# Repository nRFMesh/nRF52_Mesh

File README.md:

# Discussions
get support, give feedback or simply chat to brainstorm about ideas right here on github with s special forum for this project

https://github.com/nRFMesh/nRF52_Mesh/discussions

# New repo nRF52 Zephyr Mesh Ultrawideband
this repo is in hybernation mode and based on the nRF-SDK, new development targetting openthread on nRF52840 sensor tag based on nRF-Connect/Zephyr is ongoing on this repo https://github.com/HomeSmartMesh/sdk-hsm-sensortag

# Features

* 2.4 GHz 2 Mbps Mesh Network
  * tested with 300 packets / second
* Flash time automated database config
* Zero install time configuration
  * No association, No pairing, No factory resets
* Router = Coordinator = Repeater = Sniffer = CLI
* text serial line protocol
* Multiple Network endpoints
  * No single point of failure
* Server, Dongles, Sensors
  * Full Stack Open Source (no softdevices required)
  * HW On the shelves
  * optional DIY HW
* Alive trace routing
  * a heartbeat message that gives info about the age and RF tx/rx hops through the route

see below the [Drivers & Custom Mesh protocol](#Drivers-&-Custom-Mesh-protocol) section for the RF Protocol details

# Description
* 2 Mbps (e.g. Zgibee is at 250 Kbps to have a higher range), lowering the bitrate does not improve the range enough to get rid of repeaters, and once you need repeaters these are continuous listeners and require permanent power anyway, so the strategy is to have a repeater for every slot of the house and those repeaters can have power amplifiers and the range problem is solved keeping the high bitrate feature.
* successfull stress tests including up to 300 packets / second.
* This [nodes.json](./nodes.json) configuration file contains the short id for device unique identifier (uid64) and other configurations such as the channel, the sleep time, the required function,... Note that a python script using jLink API automate the flashing process as the uid is read every time from the attached device and matches the parameters to be flashed from the config file.
* As the short id (8 bits) is flashed, there is no association process required and all sensor devices can act as a pure beacons (no listening required) which considerably increases battery life time. We can keep arguing about the need of an acknowledged protocol for sensors logging, I do not think it is required as the feedback of battery level and rssi are both logged as well so the user knows if the sensor is in a healthy position or not.
* Router = Coordinator = Repeater = Sniffer = CLI : actually, a configuration activates the repeat functionality in case someone wants a completely stealth sniffer and this config does not require a different FW. There is nothing to coordinate as the mesh is fully dynamic with a flood and time to live concept. And every dongle has a CLI in text mode to report heard packets and takes commands as text input.
* A consequence of the simplified design allows to have multiple dongles in different locations listening to the network and reporting it to mqtt which avoids any single point of failure. By design there is no id 0 privileged coordinator and end devices do not require to know any particular associated address, they just wake up, broadcast and sleep.
* As visible in the gif animations below, Open Source SW is provided for all steps, devices firmware and server python code.

# Static Demo

* [UART : dongle firmware - directory](https://github.com/nRFMesh/nRF52_Mesh/tree/master/applications/04_uart_dongle)
* [USB : dongle firmware - directory](https://github.com/nRFMesh/nRF52_Mesh/tree/master/applications/08_usb_dongle)

    cu -l /dev/ttyACM0 -s 460800 

subscribe to topic

    mosquitto_sub -t 'nrf/#' -v | ts

start nrf_mesh [py/nrf_mesh](https://github.com/HomeSmartMesh/raspi/tree/master/py/nrf_mesh) from [raspi](https://github.com/HomeSmartMesh/raspi/) Project

    python3 nrf_mesh.py

This custom sensors RF mesh can expand to cover a home area. Onces connected to services provided in the [raspi](https://github.com/HomeSmartMesh/raspi) project, including python scripts, influxdb and grafana, the end result dashboard looks like this

---

# nRF52 Applications
    cd ./applications/

only the main applications are listed here, for further details about all applications see below the [More nRF52 Applications](#More-nRF52-Applications) section

## 01 sensor tag
    application/01_sensortag> make flash
    application/01_sensortag> make paramw

* Status : deployed > 1 year
* nRF52832 module
* Temperature, Humidity, Pressure : BME280
* Light : MAX44009
* Smooth graphana logs with cyclic broadcast ~ 30 sec => battery life ~ 6 month on CR2032
* `make paramw` detects the device uid and writes the config parameters available in [nodes.json](./nodes.json)

## 04 uart dongle
    application/04_uart_dongle> make flash
    application/04_uart_dongle> make paramw

* Status : deployed > 1 year
* buy : "nRF52832 BLE USB UART dongle"
* custom firmware and pogo-pins jtag adapter see below
* RF Mesh repeater + RF Mesh to Host interface
* `make paramw` detects the device uid and writes the config parameters available in [nodes.json](./nodes.json)

## 08 usb dongle (nRF52840-dongle)
    application/08_usb_dongle> make flash
    application/08_usb_dongle> make paramw

* buy : "nRF52840 usb dongle"
* custom firmware for RF mesh
* RF Mesh repeater + RF Mesh to Host interface
* buffered USB CDC tx and rx
* `make paramw` detects the device uid and writes the config parameters available in [nodes.json](./nodes.json)
* pogo-pins jtag adapter 3dprint : 
  * [Version two CAD Model](https://a360.co/3jr91PD)
  * [Version one Fusion360 CAD model](https://a360.co/2CDqeTA)

---

# Drivers & Custom Mesh protocol

    cd ./drivers/

## ./drivers/

Contains the custom drivers for this project from which the [mesh.c](./drivers/mesh.c) a light weight Mesh Protocol connecting all the devices using a custom RF protocol (without softdevice)
* Sleepy nodes (low power) and router nodes (always listening)
* single layer ultra simple rpotocol. App into mac with unique ids to small ids mapping
* A simple alternative to the Bluetooth Mesh and Zigbee Thread IPV6

* Low power node : Mesh node that can be a sensor Tag that wakes up on RTC or on sensor value interrupt to log a parameter. Can also be a button that wakes up on a press PIO interrupt.
* Router node : Mesh node that cooperates with the Low power nodes, the router has to be a device that keeps listening permanently on the same RF channel, this might require ~ 13 mA. Example router devices are light controllers, server’s RF dongle or USB powered sensors and status devices.
* Server : A Raspberry pi running linux. The RF signals come through the serial port or with a USB adapter, then published on MQTT, from which Python scripts inject signals on the Database, connected to Grafana web server. Note that there can be multiple router dongles connected to servers.

## Protocol Overview

The Home Smart Mesh project introduce an RF Mesh protocol which is a complete stack implementation to allow devices to communicate in a Mesh Network Topology. This protocol implementation is using the nRF SDK 15 it is using the Radio module through a modified Enhanced Shock-burst custom protocol. Implementations range from nRF24L01+ with an STM8L and STM32 to the nRF51 and nRF52 families that add features such as RSSI and bigger packets sizes.

## Protocol Description

* 100% Open source Mesh RF Stack
* Ported on STM8L, STM32, nRF51 and nRF52
* Concept designed for Low Power Nodes and Router Nodes
* Same radio channel configured for the whole network
* Single channel allows maximum power save with unlimited sleep periods, and random wake up with button press or sensor event.
* Mesh with flooding broadcast, where every message has its own configurable time to live. This brings multiple advantages of usage simplicity.
* Short addresses allow efficient packets sizes. Possibility for extensions with short address reuse and exception addresses to allow unlimited network size.
* For simplicity purpose, security is a matter of application payload content.
* The stack is so small that the RAM and ROM are left for the application logic, not requiring a network co-processor.

### Protocol Mesh Broadcast
* A simple flood mechanism is implemented where every router repeats the signal heard decrementing the time to live to avoid infinite propagation.
* Future extensions can extend the routing by gathering statistics and deciding of the optimal path in a decentralized fashion. Note that small installations in a home do not bring any significant advantage, thus the interest for a simple protocol for such use case.

### Protocol Mesh Directed messages with ack
* This type of communication uses a source and destination addresses
* Only the node recognizing itself as destination will send a packet as acknowledge
* The acknowledge packet is propagated the same way, until it reaches the source, which make it an end to end acknowledge
* If the source did not got an acknowledge back while it was requested, it can retry the transmission again.

## Packet Format

custom stack vs softdevices : This protocol is using the direct Radio module capabilities and does not require the sofdevices. The softdevices are Nordic firmware that are closed source and distributed as binaries, they have higher privileges than the user application. Softdevices guarantee that the RF functions keep always working as the user application is untrusted. This comes at a big price to pay, as the rest of the SoC cannot be properly used, no free configuration of interrupts for example, they have also a big memory footprint that prevents safe double paged firmware updates.

The configuration has discarded the usage of S0 and S1 which are intended for compatibility with other protocols which require a certain number of bits on the air that do not map to 8 aligned to form bytes in memory.

the RF Payload Format contains another software header. That is the header used to manage the packets in the mesh network.

* control: bit 7 defines whether a packet is to be broadcasted or has a target destination. Bits 6 and 5 allow safe communication with acknowledge, and a request response type. That allows the sw stack to handle the acknowledge and re-transmission. bit 3 allows streaming of messages without acknowledge.
* pid: is defining the application function which maps to a particular payload serialization
* Source and dest: are the Node Id, and are unique within every mesh. Although 8 bits, exceptions allow further reserved sizes.
* Time to live : used by the routers to know when to drop the packet.

## Alive trace routing

* All Nodes including the low power, send a periodic “alive” packet
* The initiator includes a counter that informs about the live cycle count
* Every retransmission appends information about
  * Received RSSI (Radio Signal Strength Indicator)
  * The Node Id of the Router performing the re transmission
  * Transmission power with which the packet has been re transmitted

* The “alive” packet that reaches the server’s dongle has the full route information
* Multiple paths can reach the server for the same original broadcast
* A single “alive” packet can provide link status of the complete mesh netwrok
* The signal route information is packed in a json structure
* json structures are broadcasted on the jNodes topics path

---

# Printed Circuit Boards
    cd ./boards/

Schematics, PCBs and boards headers for the SensorTag and the Dongle used by the nRF52 firmware

## ./tools/
Contains the fancy Makefile extensions that allow :
* switch power on and off using a Segger jlink
* read and write parameters matching the device's unique identifier read from the HW registers

## ./nRF5_SDK_15.0.0_prf/
This is a submodule that minifies the nRF15 SDK for the content required by this repository.
When compiling the nRF applications firmware don't forget to call the submodule update command, it is also possible to do that without git by going to the repository link, downloading it and placing it under the same path. Although if you do not use git command line at this stage, you might want to consider following a git tutorial.

    git submodule update --init

# Dependencies
* For the Raspberry pi tools and scripts see full installation steps in the [Installation](https://www.homesmartmesh.com/install/) website page
* For the nRF52 firmare :
    * GNU Tools ARM Embedded version 6 2017-q2-update, referenced from the SDK Makefile.windows
    * Python [jlink wrapper](https://github.com/square/pylink). Used in Makefile and tools of this repo, more on [pylink.readthedocs](http://pylink.readthedocs.io/en/latest/pylink.html). Note that it has to be used with a 32 bit python version referenced in the tools scripts as **C:\Python27\python.exe**. wrapper scripts already availabe in the tools directory

## Details about the nRF52 Frimware environment

* `nodes.json` is provided locally in this repo and the docker command [nodes-server.sh](./nodes-server.sh) can also serve it at http://hostname:8080/nodes.json

The parameters here are used by external tools to have a consistent undersanding of the mesh network. From simple id to name translation, to location display according to coordinates down to user data flashing.

## Cool defines and data configuration
### sdk config tool
Once in the application directory just use ```make conf``` to call a cmsis [configuration wizard](http://helmpcb.com/software/cmsis-configuration-wizard), as provided in the SDK. Note that it was here extended to make the user drivers shared and configurable as well, e.g. the I²C frequency of the **Application** in the screenshot

### Automated mesh devices configuration
 User data flashing is done with Pylink which reads in [uicr.py](tools\uicr.py) the registers of the attached device, look it up in the **config** file, retrives which parameters should be flashed, the mapping of parameters to CUSTOMER_X registers come from "uicr_map.json".

## simple board switch
The repo contais a directory for boards declaration "boards/" and a directory for applications "applications/". Although every application targets a particular board, it is possible to use any application for any other board. In the makefile a sinlge line has to be edited

    USED_BOARD := BOARD_NRF52_SENSOR_TAG

## PPI automation
The programmable peripheral interconnect is used for "real" real-time operations rf time synch,...

# nRF52 Sensor Tag
This board is based on modules, it is very simple to solder and allows selection of any other I²C sensor modules.

## Design
### Module

### Schematics
Here a screenshot of the schematics which design files are also available in the [board subdirectory](boards/nrf52_sensortag/pcb)

## Mounted PCBs
It is possible to mount either CR2032 or CR2477

It is based on a market available nRF52832 module seen below

## Low Power configuration
|Flags to clear|
--- |
| NRFX_UARTE_ENABLED |
| NRFX_UART_ENABLED | 
| UART_ENABLED | 
| UART0_ENABLED |
| NRF_FPRINTF_ENABLED |
| NRF_LOG_BACKEND_UART_ENABLED |
| NRF_LOG_STR_FORMATTER_TIMESTAMP_FORMAT_ENABLED |
| NRF_LOG_ENABLED |
* removed nrf_drv_uart.c from Makefile
* Required nRF52832 Errata [89] TWI: Static 400 uA current while using GPIOTE

## Low Power measures
| Mode | Current |
--- | --- |
| RTC + RAM | 9.6 uA |
| // + Sensors | 22 uA |
| // without TWI Woraround | 470 uA |
| Uart Log | 500 uA |
| Uart Log + HF | 700 uA |

# nRF52 Dongle
## Software
### RF to Serial Gateway
The node connected through serial port will report messages in text format
1. Local Events

Upon startup such message is sent

    nodeid:75;channel:10;reset:1

2. Listening

Upon activation of the uicr config ```is_listening``` the node starts acting as a gatewy that will report messages through serial in text mode

    rssi:-50;id:73;ctrl:0x81;src:73;alive:68;tx_power:0

3. commands requests and responses

It is possible to reconfigure the Node on runtime and manage manage a mesh network by sending messages

    cmd:0x0102
    cmd:0x<command id><arguments>

| Command id | Function | Parameters |
--- | --- | --- |
| 0x01 | Set Node Id | Node Mesh Short Identifier|
| 0x02 | Get Node Id | |
| 0x03 | Set RF Channel | 0:2400 MHz - 100:2500 MHz|
| 0x04 | Get RF Channel | |
| 0x05 | Set Tx Power | 0x04: +4dBm - 0xD8: -40dBm|
| 0x06 | Get Tx Power | |
| 0x07 | Set Bitrate | tbd |
| 0x08 | Get Bitrate |
| 0x09 | Set CRC | 0 : No CRC - 1 : 8bit - 2 : 16 bit|
| 0x0A | Get CRC |  |
| 0x0B | Set UICR | used uicr registers |
| 0x0C | Get UICR |  |

### Command examples
Set channel 10/0x0A

    cmd:0x030A

get channel

    cmd:0x04

Set Tx Power to  -4dBm/0xFC

    cmd:0x05FC

Set UICR e.g. RF Channel @ CUSTOMER[1] to channel 10

    cmd:0x0B010A

Send message, directed (not broadcast) with ttl = 2, ping(75/0x4B) from 73/0x49

    msg:0x7201494B

Send message to execute on the RF target node 75/0x4B the command Set Tx Power to -4 dBm

    msg:0x72EC494B05FC

Send message to execute on the RF target node 75/0x4B the command Set channel to 0x0A

    msg:0x72EC494B030A

Send request to execute on the RF target node 75/0x4B the command Set channel to 0x0A
The only difference to the previous example is that an intermediate ack for the request is not required before getting the response

    msg:0x22EC494B030A

### Switch between serial SERIAL and LOG over UART
run

    make conf

then switch both flags :
* nRF_Log/NRF_LOG_BACKEND_UART_ENABLED
* Application/APP_SERIAL_ENABLED
don't forget to save

### Serial mode
* NRF_SERIAL_MODE_IRQ flag is not used by the driver and has equivalent function as NRF_SERIAL_MODE_DMA

* ser_send() must be used with a variable in memory as DMA cannot read from Code in Flash

## Hardware
A usb dongle from the market that includes a **2104** serial to usb converter. Keyword search on shopping websites : **nRF52832 USB dongle**. Aka "nRF52832-YJ-17017-USB-UART"

<br/>

## From the inside

<br/>

## pinout
| nRF52 | pin |
--- | --- |
| Rx | P0.05 |
| Tx | P0.06 |
| CTS | P0.07 |
| RTS | P0.08 |
| LED1 | P0.28 |
| LED2 | P0.29 |

## Needle adapter
Making a needle adapter is made easier with 3d printing. The used pogo pin is seen below

The adapter model still in preparation can be found [here](https://a360.co/2IcKZK9). It should look something like this:

<br/>

# Raspi Host Controller Interface

## HCI MQTT Test vector

### Commands
get mesh node id of attached dongle

    mosquitto_pub -t 'cmd/request/get_node_id' -m ''

Response

    cmd/response/get_node_id {"cmd": "get_node_id", "node_id": "73"}

get channel of attached dongle

    mosquitto_pub -t 'cmd/request/get_channel' -m ''

Response

    cmd/response/get_channel {"cmd": "get_channel", "channel": "2"}

### Remote Commands
Request to set remote node 74 on RF channel 2

    mosquitto_pub -t 'remote_cmd/request/set_channel' -m '{"channel":2,"remote":74}'

Response

    remote_cmd/response/set_channel {"pid": "236", "ctrl": "0x02", "src": "74", "dest": "73", "cmd": "set_channel", "set": "2", "get": "2"}

### Actions
Ping node 74

    mosquitto_pub -t 'Nodes/79/ping' -m '{"remote":"74"}'

Aknowledge

    Nodes/79/ack 1

# More nRF52 Applications
    cd ./applications/

## 02 acell tag
    application/02_accell_tag> make flash

* Status : experimental, low battery life
* nRF52832 module
* MPU-6050 module
* interrupt pio from MPU-6050

## 03 buttons
    application/03_buttons> make flash

* Status : experiemntal, low battery life
* nRF52832 module
* x6 buttons

## 05 rotary decoder
    application/05_rotary_decoder> make flash

* buy : "600 pulses Optical Rotary encoder"
* custom wiring +5V, encoder pullups to +3.3 V
* rf timestamp synchronisation
* HW capture of timestamp
* RF Mesh log of modulo 600 position with timestamp
* 4 ms status on change, otherwise 4 s reminder

## 06 bldc 52832
    application/06_bldc_52832> make flash

* Status : RF magnetic angle control OK, rest is in development
* nRF52832 sensor tag board used
* buy : "L6234d breakout"
* custom wiring power supply 9.6 V / nRF powered with 3.3 V separately
* RF bldc control : magnetic angle, voltage ratio, speed, absolute angle

## 07 bldc 52840
    application/07_usb_dongle> make flash

* Status : preparation
* previous application "03 bldc 52832" ported to the nRF52840-dongle

# Python scripts

    cd ./raspi/

## Raspberry pi scripts moved to [github raspi](https://github.com/HomeSmartMesh/raspi) Prject

Below is a description of the `raspi` directory, but the content is no longer updated and represents a draft in compaision to the follow up project with raspberry pi services and IoT Software stack : https://github.com/HomeSmartMesh/raspi

The server's python scripts running also on a raspberry pi
* ./raspi/hue : aqara sensors from mqtt to hue light automation through the hue gateway REST API
* ./raspi/rf_uart : the interface to the serial port that transfers data between MQTT and the RF mesh
* ./raspi/heat : eurotronics through zigbee2mqtt automation from aqara zigbee2mqtt windows contact sensors
* ./raspi/bathroom : fan automation controlled with button, shelly light switch and humidity sensor
* ./raspi/conbee : the ConBee script to turn the Xiaomi Zibbee devices events into MQTT
* ./raspi/rf_stm32 : interface to leagacy devices, bed heater and retro light
* ./raspi/ruler/ : json configurable rules through sensors and actuators MQTT topics and a separate python rules file
* ./raspi/influx/ : the [influx](https://www.influxdata.com/time-series-database/) client that listens to MQTT and grabs standard sesnors patterns to be sent to the database
* ./raspi/grafana : [Grafana](https://grafana.com/grafana) is used as a dashboard, it is a webserver interface that is installed on the raspberry pi (or on the docker image). Some dashboards examples are provided in this directory, where the queries are matching the way how the influx client has recorded the sensors data. 
* ./raspi/wemo/ : The wemo switch smart socket interface, provides power sensing and sends the Watt value to MQTT
* ./raspi/milight : The milight RF gateway client (require the wifi to RF milight bridge HW)
* Data collection into a time series database 
    
# Home Smart Mesh detailed design

Functions call graph. Fifos dataflow between interrupts and main loop.

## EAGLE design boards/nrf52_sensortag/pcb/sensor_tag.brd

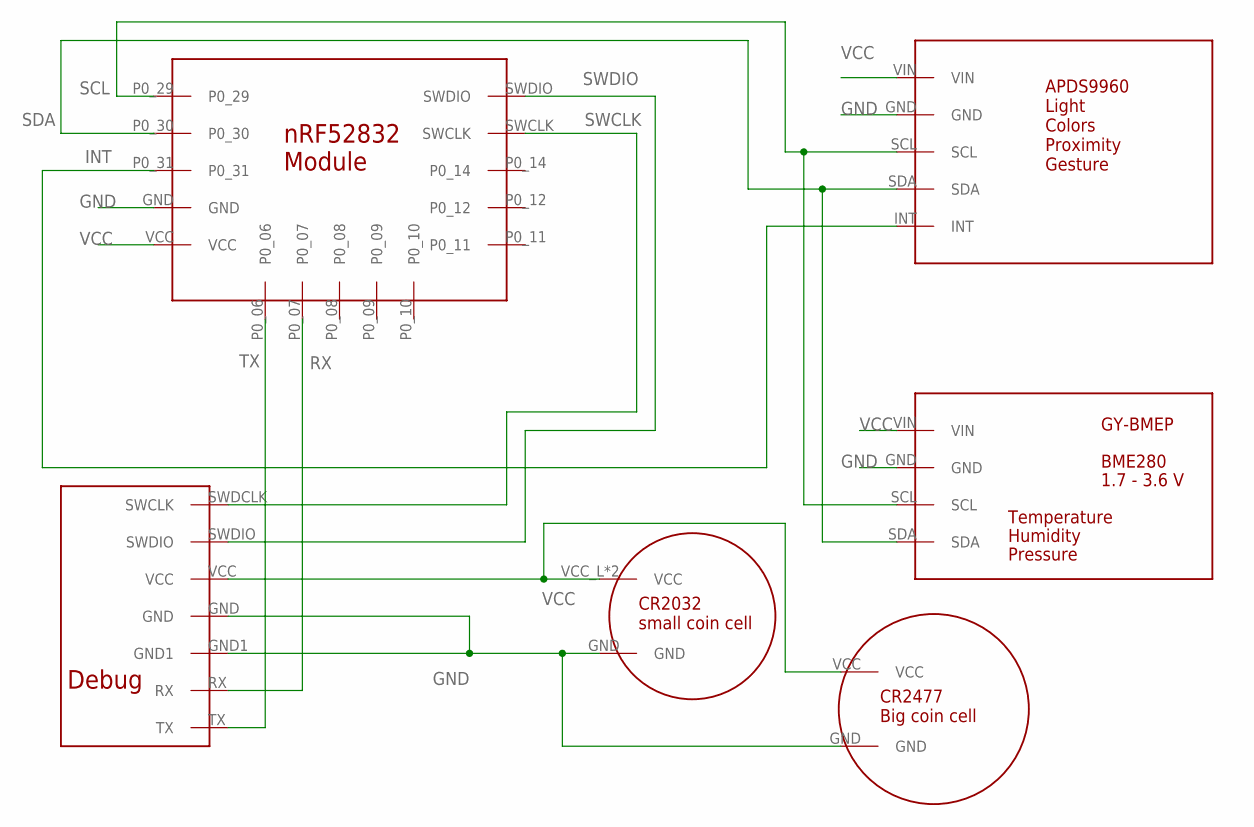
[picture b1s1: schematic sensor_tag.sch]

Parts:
U$1: GY-BMEPGY-BMEP-NOHOLE; GY-BMEP-NOHOLE
U$2: APDS9960_MODULEAPDS9960-FULL; APDS9960-FULL
U$3: NRF52832_MODULENRF52832_MOD_SMALL; NRF52832_MOD_SMALL
U$4: CR2032; CR2032_SMD
U$5: NRF_TAG_DEBUG
U$6: CR2477

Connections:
GND: U$1.GND, U$2.GND, U$3.GND, U$4.GND, U$5.GND, U$5.GND1, U$6.GND
INT: U$2.INT, U$3.P0_31
RX: U$3.P0_07, U$5.RX
SCL: U$1.SCL, U$2.SCL, U$3.P0_29
SDA: U$1.SDA, U$2.SDA, U$3.P0_30
SWCLK: U$3.SWCLK, U$5.SWDCLK (SWCLK)
SWDIO: U$3.SWDIO, U$5.SWDIO
TX: U$3.P0_06, U$5.TX
VCC: U$1.VIN, U$2.VIN, U$3.VCC, U$4.VCC_L (VCC), U$4.VCC_R (VCC), U$5.VCC, U$6.VCC

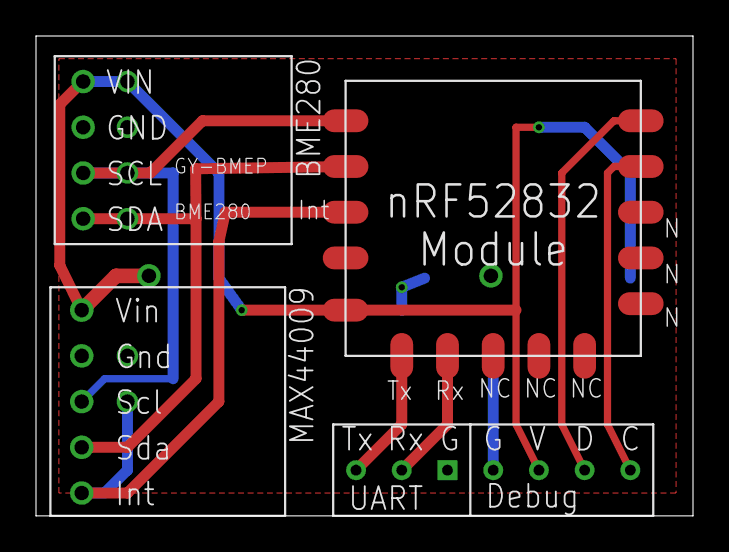
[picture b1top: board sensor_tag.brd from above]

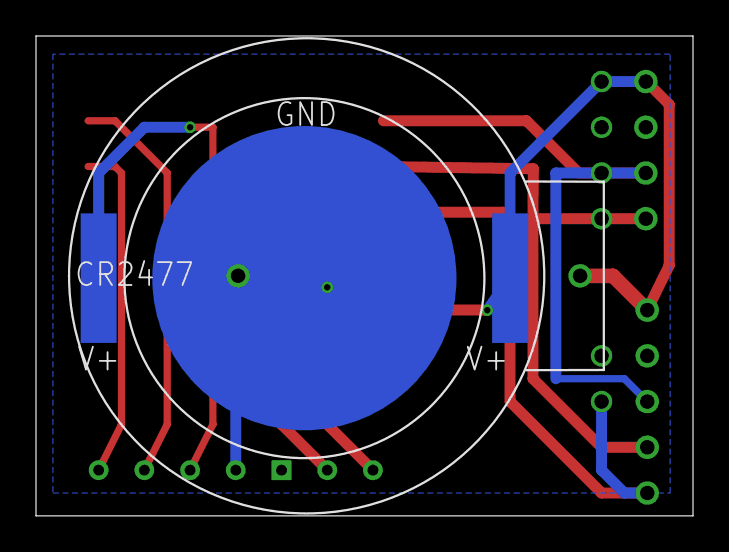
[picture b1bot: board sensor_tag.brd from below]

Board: 2 copper layers, 36.5 x 26.7 mm, 6 parts (2 on the bottom side), 9 nets.

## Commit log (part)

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2018-05-13 first takeover from IoT_Frameworks with multipl applications structure
2018-05-13 moved boards out of sdk with boards directory
2018-05-13 including media and updating readme using it
2018-05-15 working nRF dongle testeed with RF and UART
2018-05-18 dfu tools and low power testing
2018-05-18 Low power from ~ 1000 uA down to 22 uA
2018-05-19 small update readme
2018-05-21 mesh switching between TX and RX modes
2018-05-21 updated gitignore
2018-05-24 serial uart sending immidiate and with buffers
2018-05-24 success in rssi log
2018-05-25 pogo pin adapter image
2018-05-26 update to mesh handler usage
2018-05-26 fixed wrong listening default interpretation
2018-05-29 working Tx Rx HSM msg in mesh and LOG config
2018-05-30 multiple reception step 1 achieved
2018-05-30 rx serialise of alive with rssi, power and live counter
2018-05-30 minor reduction
2018-05-30 resolved uart tx conflict and working repetition
2018-05-31 quick tx rx switch no dis-enable
2018-05-31 working serial Tx with event handler
2018-05-31 UART lines collection and mirror, Doxygen config, unified UICR config
2018-05-31 serialisation to uart of main app protocols ids
2018-06-01 #3 read params before writing
2018-06-01 added parsing of most of app rx protocols
2018-06-01 serial port protection with mutex
2018-06-03 #3 set back crc usage tested
2018-06-03 Fixed gnd design issues and new gerber order
2018-06-06 continuous RF Rx support
2018-06-07 python rf uart hci and mqtt combined
2018-06-07 preparing publish
2018-06-08 rf to mqtt python running
2018-06-08 fix rssi mqtt topic
2018-06-09 added battery support
2018-06-09 fix light unit to be float lux
2018-06-11 message hci send and ping ack success
2018-06-12 success in RTX delay and count with timer
2018-06-13 handling remote command executing debug step 1
2018-06-13 tested request response remote execute command
2018-06-14 alive path signal tracing protocol working
2018-06-15 alive json with rtx on jNodes
2018-06-17 MQTT request and response for remote command execution
2018-06-19 first three single node sceane
2018-06-20 no default port
2018-06-20 wizard with config bootstrap and threejs 3d view
2018-06-21 bugfix wrong alive on reroute function
2018-06-21 document new uicr command
2018-06-21 Orbit and using classes
2018-06-23 sensor alive and mesh reset for mqtt
2018-06-23 +4 dB for dongles
2018-06-23 hci client config
2018-06-24 get node id, and button in mqtt
2018-06-25 mpu6050 bringup on the nRF52 Sensor Tag with nrf_drv_twi
2018-06-25 test old accell protocol log without accx params
2018-06-27 mpu 6050 debug
2018-06-27 pcb BOM
2018-06-27 using javascript modules
2018-06-28 dynamic nodes table
2018-06-29 takeover of python clients
2018-06-29 fix unavailable devices
2018-06-29 added cfg
2018-06-30 moved influx and new nodes
2018-06-30 updated generic config for rf_uart
2018-07-01 readme and dashboards
2018-07-19 acceleration to angle ruler
2018-07-19 python3 for ruler
2018-07-21 python compatibility and requirements
2018-07-22 dongle leds blink and power consume
2018-07-22 new nodes, safe angle
2018-07-22 debugging motion interrupt
2018-07-23 motion sensor app started logging motions
2018-07-28 fixed exception log
2018-07-28 using python3
2018-07-29 right socket and dir name
2018-08-04 motion text through rf
2018-08-04 change raspi_run mode
2018-08-04 accell motion events adjust
2018-08-04 back to python 2
2018-08-11 default nodes config path
2018-08-14 log coherency and first file creation bugfix
2018-08-14 config error adjustments
2018-09-01 hue started
2018-09-22 conbee websockets notifications from zigbee sensors
2018-09-23 conbee xiaomi to MQTT json
2018-09-24 cube action on mqtt with event and analog
2018-09-24 conbee examples
2018-09-25 chaging topics to model id
2018-09-25 fixed modelid
2018-09-25 updated config
2018-09-25 config adjust
2018-09-29 cleaning config and files
2018-09-29 fixed MQTT loop
2018-09-30 updated dashboards and config
2018-09-30 removed STM8L and unused Milights
2018-09-30 renaming the Cube
2018-09-30 missing hue names
2018-09-30 fixed json loads bug
2018-09-30 introducing the heatr to MQTT
2018-10-01 added stm32 brightness from MQTT
2018-10-02 added heat topics
2018-10-04 bugfix msg. not required
2018-10-05 node added
2018-10-05 updated wemo bed name
2018-10-05 configurable polling
2018-10-05 update stm32
2018-10-06 mqtt on off callback for heater
2018-10-11 added switch
2018-10-11 added light and presence
2018-10-13 send model id not nodeid
2018-10-13 motion sensing stairs entrance from top
2018-10-13 added open close to conbee
2018-10-13 declaration in nodes no longer necessary
2018-10-13 added zigbee path on mqtt
2018-10-15 updated motion and cube events
2018-10-15 same naming
2018-10-18 Ordered dict and motion fix
2018-10-18 testing conditional lighting
2018-10-18 auto brightness adjust
2018-10-18 half remote lights
2018-10-19 added Xiaomi small switch
2018-10-19 added motion sensors subscriptions and id tests
2018-11-02 add entrance light with the new switch
2018-11-02 aqara switch for lights upstairs
2018-11-03 zigbee swithc to esp bed heater
2018-11-06 handle http 404 error
2018-11-06 sunset sunrise
2018-11-11 bug fix bat stat message
2018-11-12 new dashboards
2018-11-12 esp32 python ruler
2018-11-15 added zigbee2mqtt forward to influxdb
2018-11-17 Kitchen Move
2018-11-17 Kitchen move on hue
2018-11-20 prepare for mano use of influx and zig
2018-11-20 influx custom subscription
2018-11-20 configurable zigbee mqtt root topic
2018-11-20 fixed action fields for zig cube
2018-11-20 cube in subscriptions
2018-11-20 changed mano port as default in config
2018-11-20 hassio hue
2018-11-20 moved hue to rfreserv
2018-12-02 fixed click selection
2018-12-02 esp32 port to rfserv
2018-12-02 dashboards, design and shift wemo to mano
2018-12-02 switching hassio's mqtt to mano
2018-12-02 remove ruler
2018-12-06 influx whitelisting mqtt topics
2018-12-08 upstairs heating percent ruler
2018-12-09 added dashboard
2018-12-09 double click on off for leds
2018-12-15 RGB led panel testing
2018-12-21 led panels wavelets
2018-12-21 retrolight with zigbee buttons
2018-12-22 control with zigbee
2018-12-22 zig tree light control
2018-12-24 export csv from influx
2018-12-24 quotes error
2018-12-24 test different
2018-12-24 year convenient notation
2018-12-28 christmas rename
2018-12-28 shifted wemo to mqtt module usage
2018-12-29 nRF52840 rov attempt failing
2018-12-29 subomodule for nRF52840
2018-12-29 python tester
2018-12-29 bldc with timers and ppi compiling
2018-12-29 pio 29 toggling with ppi
2018-12-29 pwm running with right polarity
2018-12-29 bldc py test turning
2018-12-31 timestamp running
2018-12-31 logging through rf 1.3 ms tested
2018-12-31 moved rover python and webapp to server raspi repo
2019-01-01 added debug dongle switched to sensor board max payload size increase disable rtc alive rov handle commands rf and uart
2019-01-01 reinit uart on slow consumption and drv error
2019-01-01 drv error fix with reinit
2019-01-03 zig purge influx fix battery type
2019-01-04 qdec fail pio decoder
2019-01-12 rf sync the timer
2019-01-13 added bare nrf board for debug custom840.h unused loader script nrf52840 without bootloader fixed led colors assignment debug start with blink and debug pio
2019-01-14 debug and cleaning
2019-01-14 renaming of applications
2019-01-14 debugging the usb won't start
2019-01-18 compile success with Thread SDK
2019-01-18 correctly running usb enabled with '0'
2019-01-19 usb and rf logging
2019-01-19 high freq rf to usb no reset
2019-01-19 part 2
2019-01-19 auto usb write enable disable
2019-01-19 usb rx running but with first character lost
2019-01-20 fixed usb rx with immediate rx event
2019-01-24 timer capture with ppi from gpiote
2019-01-25 group autodisable experiment
2019-01-25 sync with ppi works but main loop inconsistent
2019-01-25 updated readmes with svg export
2019-01-25 path fix
2019-01-26 compare timer running with sw shift
2019-01-26 compil fix
2019-01-26 automated compare loop with ppi
2019-01-26 bldc and encoder in sync with drift
2019-01-26 bldc speed control
2019-01-27 disable dining multifunction
2019-01-27 update readme with applications images
2019-01-27 readme and design
2019-01-27 testing cpp
2019-01-29 simple test fifo no long frames runs
2019-01-29 success tx more than 64 bytes with ring buffer
2019-01-30 usb cpp wrapper
2019-02-02 moved app to sensored bldc with new nodes file
2019-02-03 moved get_this_node_id to utils
2019-02-03 compiling bldc cpp first port
2019-02-03 moved bldc to class with constructor
2019-02-03 set pole cleaning and usb rx simple command
2019-02-03 compiling but simple no string
2019-02-03 testing compil with std::string
2019-02-03 added c++ std library
2019-02-03 success with line-mqtt-json motor command
2019-02-04 fine adjustments of line protocol and topics
2019-08-15 added rssi info from jNodes to max in Nodes
2019-08-29 added flat rooms model and edited sensors position
2019-09-01 Added room names and Lighting per room
2019-09-02 modified rights
2019-09-05 added living heat
2019-09-07 bedroom light
2019-09-08 heat management system
2019-09-08 removed forgotten printf
2019-09-08 changed contact initial value
2019-09-21 bathroom light and office
2019-09-22 fixed names
2019-09-22 blacklist filed last_seen
2019-09-23 last_seen management
2019-09-23 adjusted names
2019-09-28 influx and light liv bed
2019-09-29 updated dashboards
2019-10-03 fixes for flashing
2019-10-03 fixed regression of Makefile for shift to cpp project before commit
2019-10-04 updated tags
2019-10-05 use tree instead of sunrise
2019-10-07 renamed sensor
2019-10-10 repaired buttons
2019-10-13 fixed heating names
2019-10-13 added influx windows subscription
2019-10-14 renamed buttons
2019-11-16 updated bed temp management
2019-11-16 right name fix for bed heat button
2019-11-17 consistent nrf tags naming
2019-11-19 rename office light
2019-11-23 rf uart config and light buttons names
2019-11-30 bathrrom manager first script
2019-11-30 fan relay fix
2019-11-30 hysteresis protection
2019-11-30 configurable parameters
2019-12-01 introdiced the bathroom button
2019-12-01 string playload decode fix
2019-12-01 shelly on influx
2019-12-01 long press for fan
2019-12-01 log info only
2019-12-10 updated names
2019-12-19 fixed tested temperature -1 bug
2019-12-19 reconfig
2019-12-19 fix hue hardcoded light in init
2020-01-04 change floating voltage name to voltage not battery
2020-01-04 generic windows sensor contact list for heat control
2020-01-10 fixed light function call fan bug
2020-01-10 info level for humidity sensors
2020-01-11 info log level for stop conditions
2020-02-02 humidity bug old value checked by condition
2020-02-06 added bathroom shellies monitors
2020-02-08 added shelly entrence
2020-02-09 home status on shelly led
2020-02-09 added heat monitor
2020-02-09 case sensitive Apertures
2020-02-09 default status
2020-02-11 not delta but pi heating demand check
2020-02-15 added shelly bed heater
2020-02-15 bathroom low button
2020-02-22 added power monitors
2020-02-22 fix config bug
2020-02-22 added entrance
2020-02-24 update entrance ip
2020-03-22 influx naming
2020-03-29 added tv set and ethernet repeater
2020-03-29 forgot power, now added
2020-03-29 added pc and sonos
2020-03-29 sonos sat not sound
2020-05-10 added nrf mesh py server
2020-06-09 update log level
2020-06-14 tag friendly name with small case
2020-06-18 first step for nodes as a service
2020-06-19 docker serve nodes
2020-06-19 publish nodes file ony moved on top
2020-06-19 moving to served config
2020-06-19 rename config
2020-06-20 updated readme doc with features and grafana dashboard
2020-06-20 moved images abd removed doc ignore and folder
2020-06-20 added protocol doc to the readme
2020-06-20 added info about paramw and buffers
2020-06-21 removed mesh_wizard as it moved to its own project smart home 3d webapp
2020-06-21 removed deprecated as moved to new raspi repo
2020-06-22 removed unused config from deprecated server
2020-07-03 update sensor location and name
2020-07-12 added presence for light
2020-08-02 turned mesh_controller into a service
2020-08-03 removed duplicate folder with raspi repo
2020-08-30 documented the new pogo adapter version
2021-02-07 Makefile only broken rest is fine
2021-05-08 note about Thread sensor tag
2021-07-03 added discourse annouce
